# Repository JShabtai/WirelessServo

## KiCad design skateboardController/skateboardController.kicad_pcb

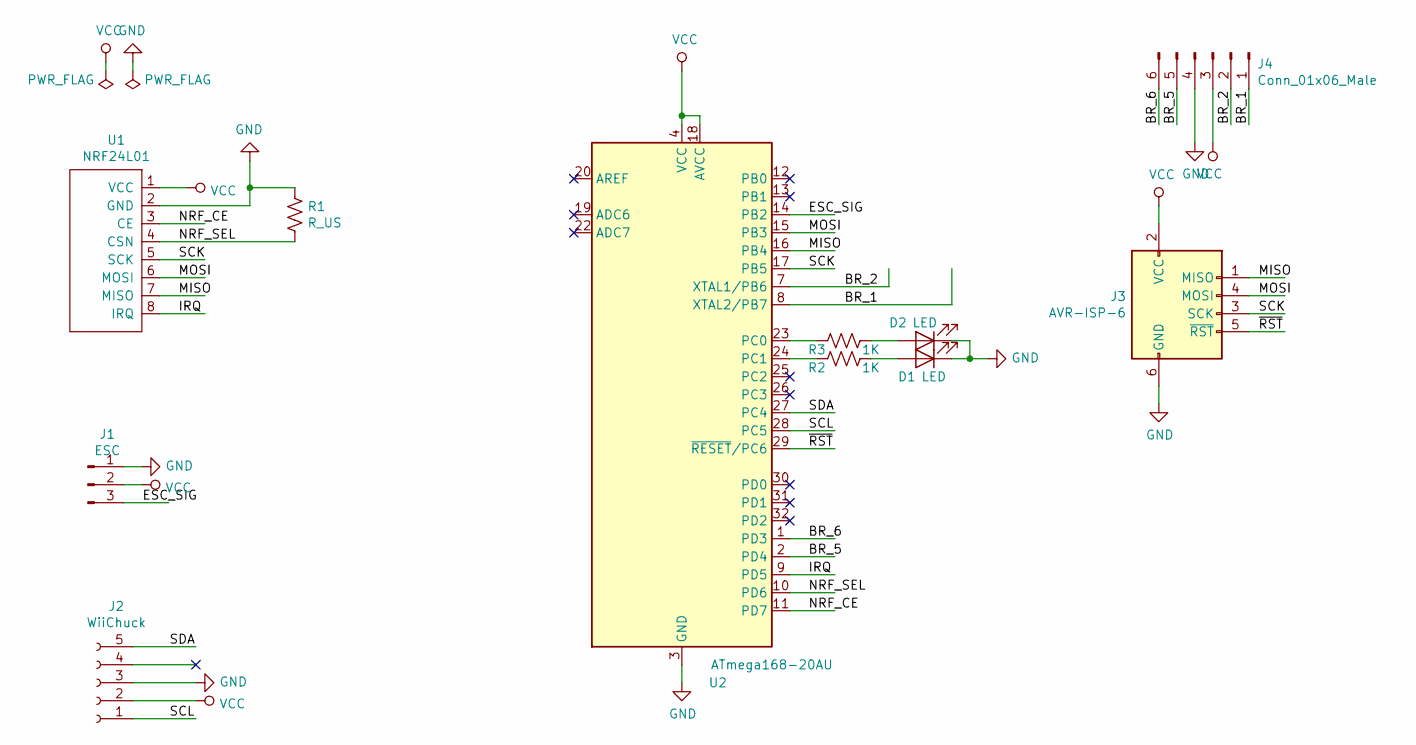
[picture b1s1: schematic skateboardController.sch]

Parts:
D1, D2: LED; LED_0603_1608Metric_Pad1.05x0.95mm_HandSolder
J1: ESC; PinHeader_1x03_P2.54mm_Vertical
J2: WiiChuck; PinHeader_1x05_P2.54mm_Vertical
J3: AVR-ISP-6; IDC-Header_2x03_P2.54mm_Vertical
J4: Conn_01x06_Male; PinHeader_1x06_P2.54mm_Vertical
R1: R_US; R_0603_1608Metric_Pad1.05x0.95mm_HandSolder
R2, R3: 1K; R_0603_1608Metric_Pad1.05x0.95mm_HandSolder
U1: NRF24L01; NRF24L01_SMD
U2: ATmega168-20AU; TQFP-32_7x7mm_P0.8mm

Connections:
/BR_1: J4.1, U2.8 (XTAL2/PB7)
/BR_2: J4.2, U2.7 (XTAL1/PB6)
/BR_5: J4.5, U2.2 (PD4)
/BR_6: J4.6, U2.1 (PD3)
/ESC_SIG: J1.3, U2.14 (PB2)
/IRQ: U1.8 (IRQ), U2.9 (PD5)
/MISO: J3.1 (MISO), U1.7 (MISO), U2.16 (PB4)
/MOSI: J3.4 (MOSI), U1.6 (MOSI), U2.15 (PB3)
/NRF_CE: U1.3 (CE), U2.11 (PD7)
/NRF_SEL: R1.2, U1.4 (CSN), U2.10 (PD6)
/SCK: J3.3 (SCK), U1.5 (SCK), U2.17 (PB5)
/SCL: J2.1, U2.28 (PC5)
/SDA: J2.5, U2.27 (PC4)
/~RST: J3.5 (~RST), U2.29 (~RESET~/PC6)
GND: D1.1 (K), D2.1 (K), J1.1, J2.3, J3.6 (GND), J4.4, R1.1, U1.2 (GND), U2.3 (GND), U2.5 (GND), U2.21 (GND)
unnamed: D1.2 (A), R2.1
unnamed: D2.2 (A), R3.1
unnamed: R2.2, U2.24 (PC1)
unnamed: R3.2, U2.23 (PC0)
VCC: J1.2, J2.2, J3.2 (VCC), J4.3, U1.1 (VCC), U2.4 (VCC), U2.6 (VCC), U2.18 (AVCC)

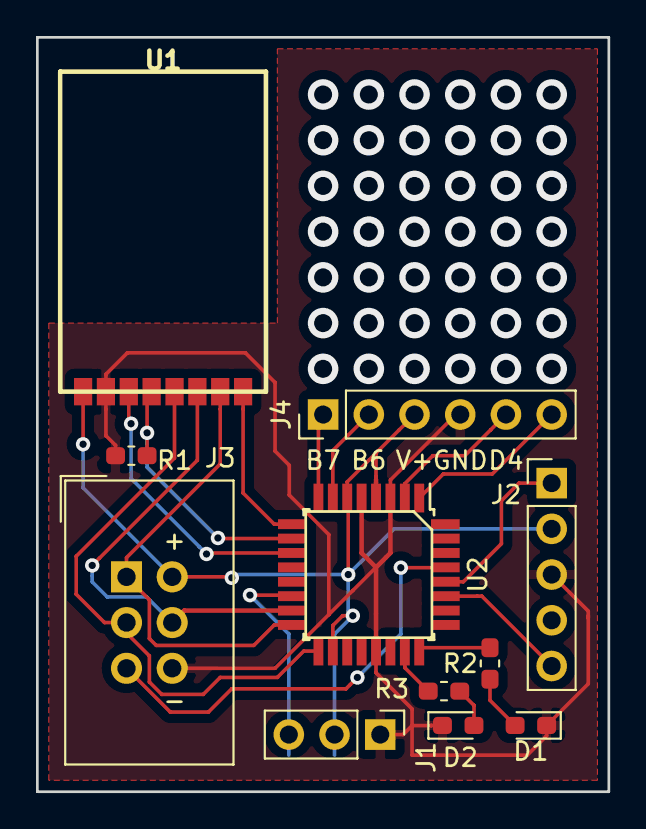
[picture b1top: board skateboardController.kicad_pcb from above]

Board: 2 copper layers, 31.8 x 41.9 mm, 11 parts (0 on the bottom side), 20 nets.

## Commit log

2019-05-26 Added PCB v0.1
2019-05-26 PCB v0.2 - Fixed proto grid
